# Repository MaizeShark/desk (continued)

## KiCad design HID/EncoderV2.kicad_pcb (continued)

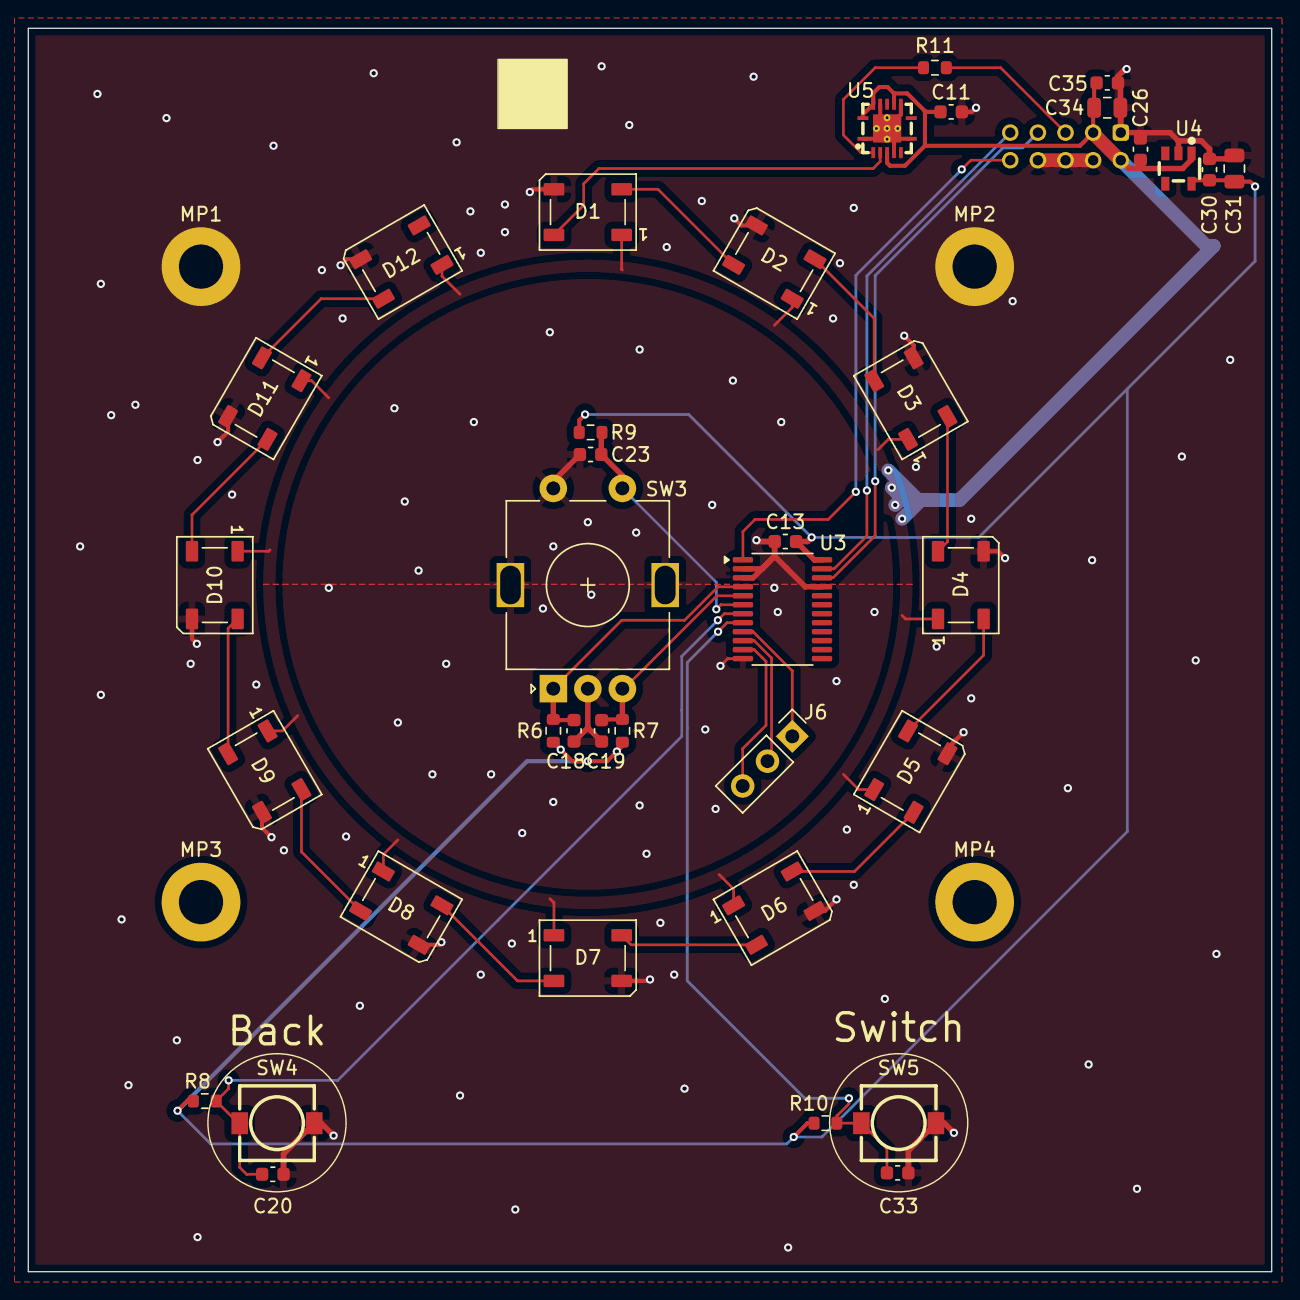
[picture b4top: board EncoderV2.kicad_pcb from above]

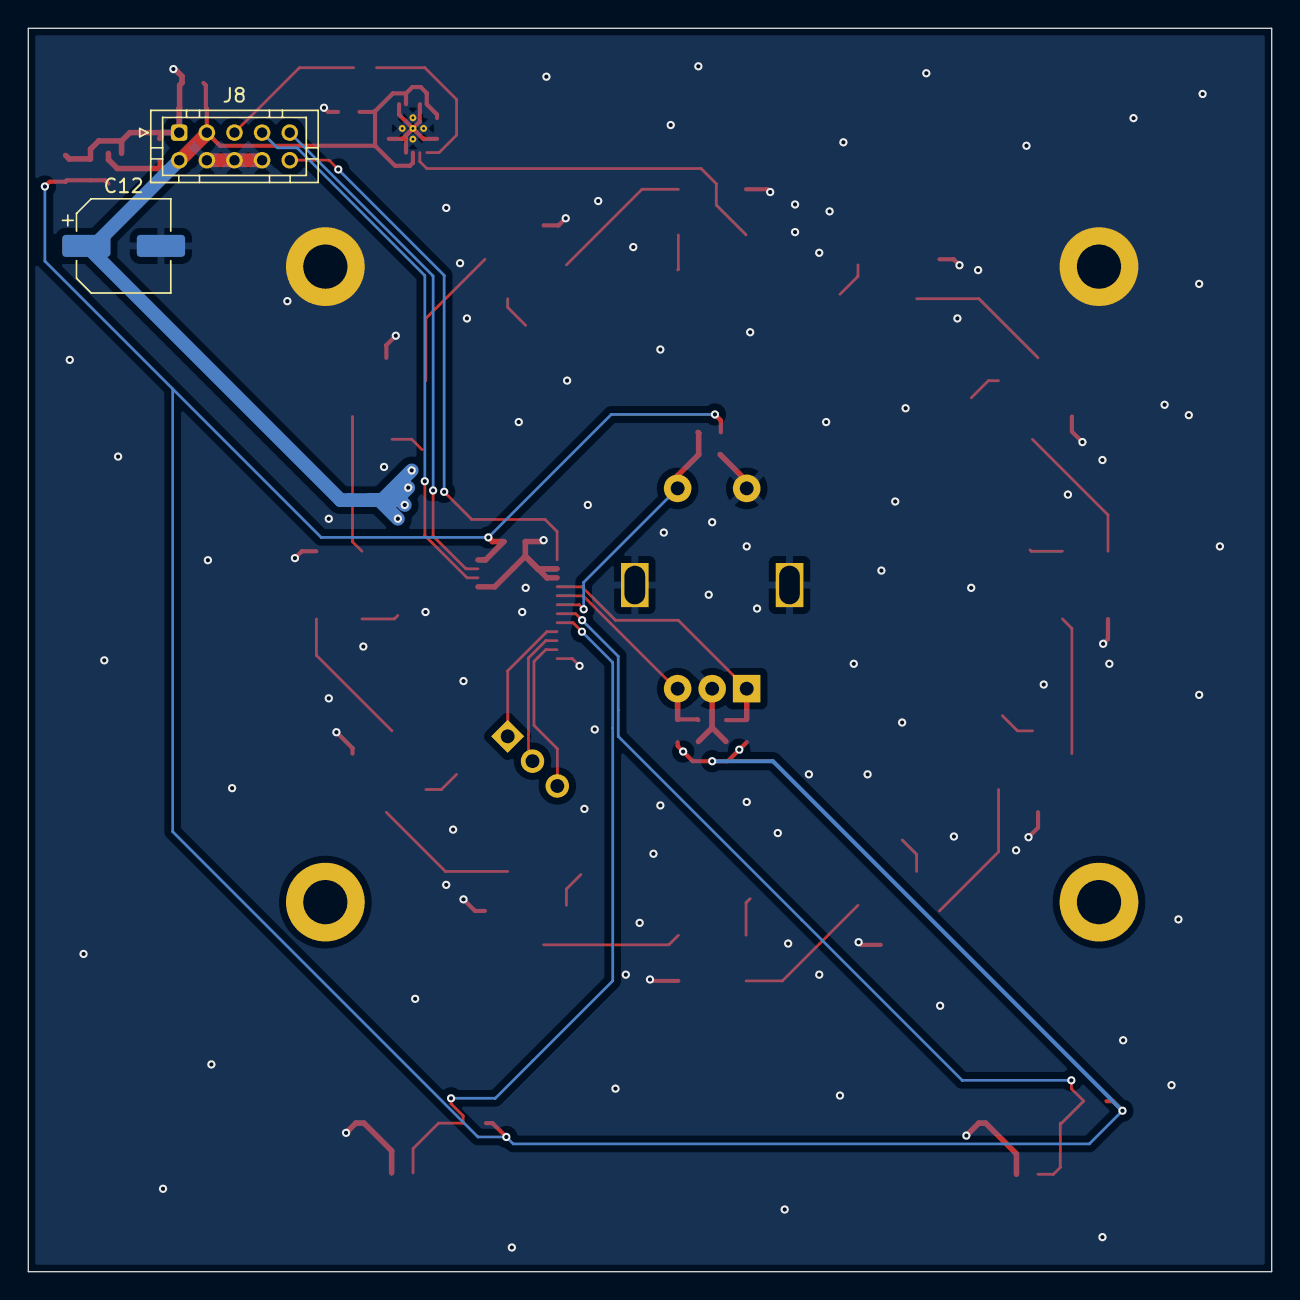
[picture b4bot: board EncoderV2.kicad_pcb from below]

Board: 2 copper layers, 90.0 x 90.0 mm, 43 parts (2 on the bottom side), 28 nets.

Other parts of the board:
MP1, MP2, MP3, MP4: MountingHole_3.2mm_M3_ISO7380_Pad

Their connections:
GND: MP1.1, MP2.1; also elsewhere on the board

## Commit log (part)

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2025-08-20 added KiCad files
2025-08-20 added Raspi, ESP32 etc
2025-08-25 Initial commit of project source code
2025-08-25 feat: Improve .gitignore and remove tracked binaries/backups
2025-08-25 fix: Correct .gitignore for #auto_saved_files and update project
2025-08-26 updated schematics
2025-08-26 updated schematics and added MSP4030 Docs
2025-08-27 Add image processing script and assets for thumbnail generation
2025-08-27 updated button name and gitignore to (for now) block lvgl stuff
2025-08-29 Add Docker setup with image processing and MQTT integration
    - Create Dockerfile and docker-compose.yml for containerized application
    - Renamed bild_generator.py to image.py
    - Add font license documentation for Delius font
    - Update requirements.txt for necessary dependencies
    - Introduce .dockerignore and .gitignore for better file management
    - Remove unused image and script files
2025-08-29 Refactor thumbnail resizing to use ImageOps.fit for better aspect ratio handling
2025-08-29 Update image.py
    changed font location
2025-08-30 Add example.env for configuration
2025-08-30 Add MPRIS to MQTT bridge implementation and service configuration
2025-08-30 Add README.md for service documentation and update poll interval to 45 seconds
2025-08-30 Enhance playback status check to publish MQTT message when no active playback is found
2025-08-31 Add album art URL to player information and update JSON payload structure
2025-08-31 Enhance playback status check to handle MQTT status updates and update image creation logic
2025-09-25 Update README and main.py for enhanced image generation and API client setup
    - Updated README to reflect support for RaspiOS in installation instructions.
    - Modified main.py to added length and elapsed time to player info.
    - Implemented caching and rate limiting for Spotify and Jellyfin API calls.
    - Enhanced image creation function to avoid unnecessary processing and publish improved MQTT messages.
2025-09-25 Saving my work on PCB and other files
2025-09-25 Enhance playback status check to include logging for skipped Spotify and Jellyfin polls
2025-09-25 Refactor main.py and example.env for improved logging and configuration management
2025-09-25 Cleanup docker-compose.yml and refactor main.py for improved readability and structure
2025-09-25 Enhance Spotify polling with retry logic and error handling for rate limits
2025-09-25 Refactor PlaybackManager to use a constant for Spotify API retry count and improve error handling for rate limits
2025-09-26 Refactor PlaybackManager to ensure track item is checked before accessing its properties
    - Added check for `results.get('item')` in `PlaybackManager.current_playback()`.
    - Updated image loading with a user-agent header for compatibility.
    - Added type ignore comment for mqtt.Client initialization.
    UI/Docker/main.py
2025-09-26 feat: Add MQTT as a playback source and improve image fetching
2025-09-26 Add MQTT remote control for media player
    Implement the ability to control the media player (play/pause, next, previous, seek) via new MQTT topics under `music/control/`.
    Refactored the script to use the `pydbus` library directly instead of shelling out to `playerctl`, making it more robust and efficient.
2025-11-26 Update PCB/Schematic files, scripts and just refractured
2026-01-07 Stop tracking large binary files
2026-01-07 Add GNU GPL v3 license
    Added the GNU General Public License version 3 to the project.
